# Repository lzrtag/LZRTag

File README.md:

# LZRTag
### ESP32-Based Lasertag

Ever wanted to set up your own system of Lasertag?
Interested in having an easily modifiable system to create your own gamemodes and styles with?
Or just looking for a cool project to try out?
Well, why not take a spin at this!

*Note:* This project is not in serious development. I (Xasin) take no responsibility for what is done with this code, and I can't guarantee it'll do exactly what I tell it to (even if I try to give it treats >:c)
However, it is a fully functional system, if you know how to use it, and it has proven itself
to be pretty reliable and useful!

## The components
In order to have a functional game, you will need at least the following:
- Two or more soldered Lasertag Sets
- A WiFi access point or a newtwork of points throughout the arena.
- A MQTT Server, preferrably in the local network, to reduce ping.
- And a system running Ruby 2.4 or better, to run the Lasertag Backend and your gamemodes

## The Electronics
*Attention:* The electronics aren't necessarily beginner-friendly. I've designed them with components no smaller than a TSOP package or a 0805 resistor, but the newer versions of the hardware do include two QFN Packages - one for a optional IMU, so it can be left out, and one for a standard I2S audio chip, for which you can use any breakout board that supports 44100Hz, 16 bit playback. If you have a hot air gun,
definitely make use of it!

The electronics are based around the ESP32, a fairly cheap, powerful, WiFi and Bluetooth capable chip. The PCB includes all necessary support structures, including a battery charge circuit and a USB to UART converter to reprogram and debug the ESP.
It comes with the following hardware:
- The ESP32 plus beefy voltage regulation, ESD protection, etc. It ain't gonna break!
- A MAX I2S decoder + amplifier, for on-board, high quality audio.
- A LSM6D IMU, to detect movement, collisions, gestures, etc.
- Peripherals to receive and send IR Signals (documented here: TODO)
- Feedback in the shape of WS2812 LEDs and a vibration motor
- Trigger, Gun Select and Reload buttons.

The vest connection is exposed with a D-SUB connector, and I2C lines are available to make
more complex add-ons easier to achieve. There's also a I2C breakout connection on the PCB itself!

The Vest itself can be as simple as a couple of Vishay 40kHz IR receivers and WS2812 LEDs, but
there is a connection for vest-specific haptic feedback, and via the I2C connection it's easy to add
more complex features.

To solder one, check out the Aisler project here: https://aisler.net/p/QLILZEMV
Or head to the "Electronics" folder and generate your own Gerber files!

## The Casing
The 3D printed casing I designed is totally optional - the electronics can be easily fitted into any other casing, provided it has space for a switch, a speaker and a couple of LEDs!
However, if you do want to print it out, there's the Fusion360 page here: https://a360.co/2Lbm2zJ

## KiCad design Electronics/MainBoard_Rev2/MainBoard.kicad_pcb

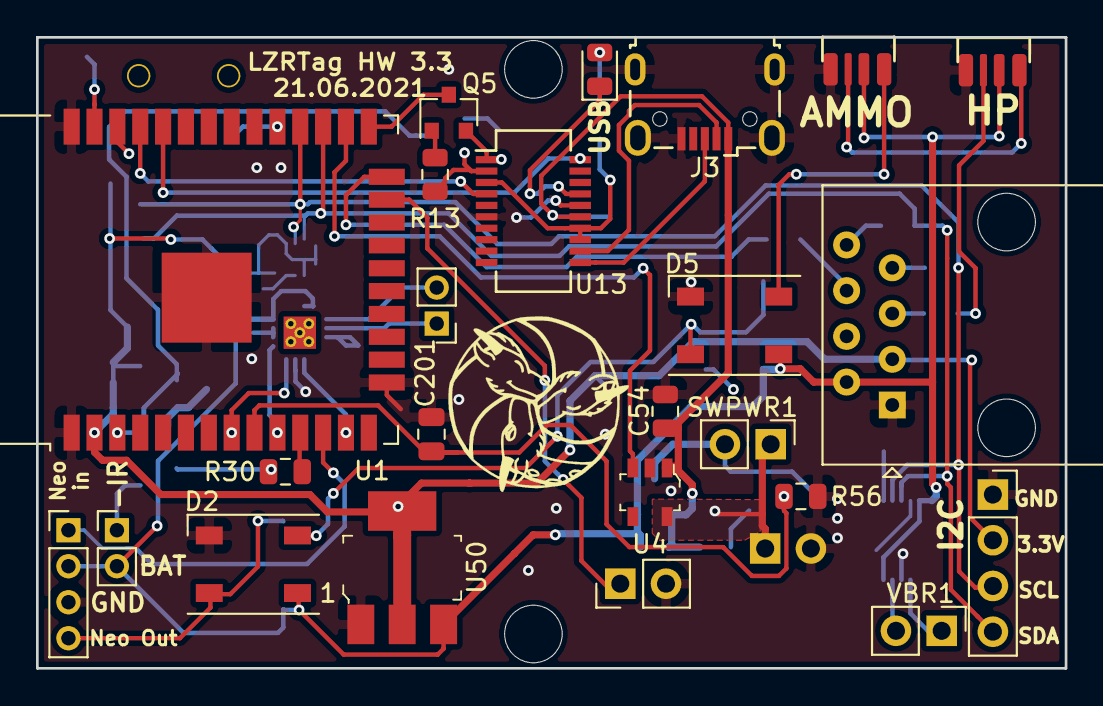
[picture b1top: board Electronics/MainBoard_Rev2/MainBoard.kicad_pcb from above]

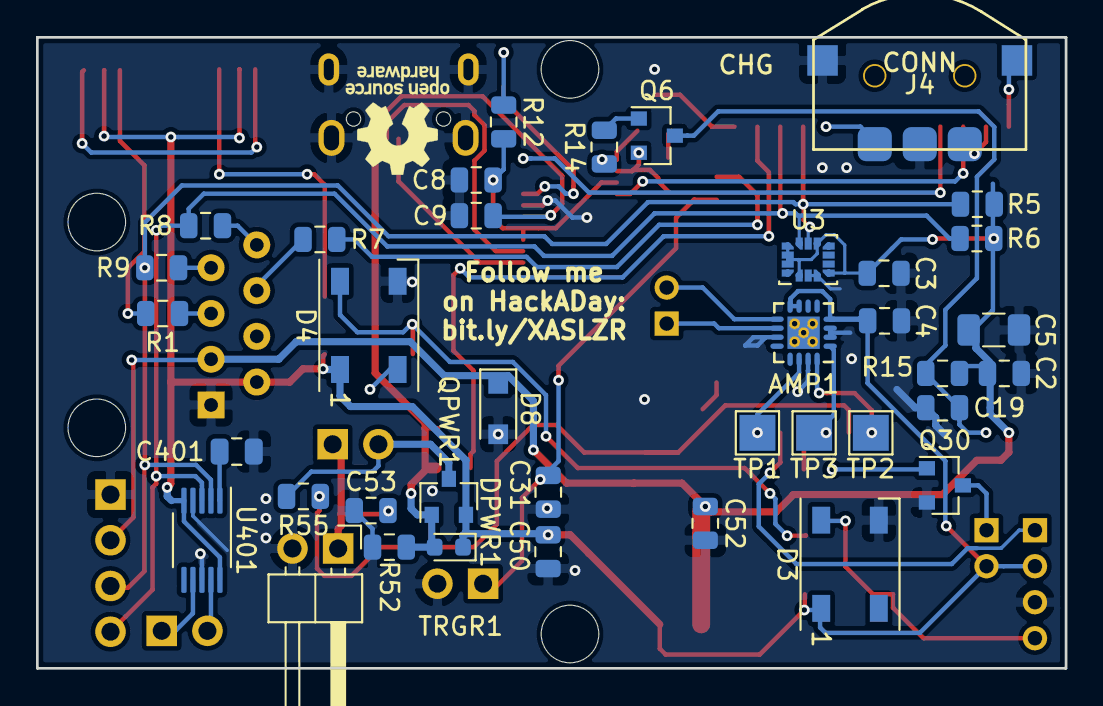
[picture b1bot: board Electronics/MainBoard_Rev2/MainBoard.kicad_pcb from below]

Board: 2 copper layers, 57.2 x 35.1 mm, 67 parts (40 on the bottom side), 49 nets.

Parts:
AMP1: MAX98357A; QFN-16-1EP_3x3mm_P0.5mm_EP2.7x2.7mm_ThermalVias
BT1: Battery_Cell; PinHeader_1x02_P2.54mm_Horizontal
C2, C3, C8, C19, C31: 100nF; C_0805_2012Metric
C4, C9, C52, C53: 10uF; C_0805_2012Metric
C5: 47uF; C_1206_3216Metric
C50, C54, C401: 1uF; C_0805_2012Metric
C201: 0.1uF; C_0805_2012Metric
D1: COM-12999; PinHeader_1x04_P2.00mm_Vertical
D2, D3, D4, D5: WS2812B; LED_WS2812B_PLCC4_5.0x5.0mm_P3.2mm
D8: D_Zener_ALT; D_SOD-123F
D30: SFH4545; PinHeader_1x02_P2.00mm_Vertical
D401, D402: IN-PI42TAS
DPWR1: D_Schottky; D_0603_1608Metric
DUSB1: LED; LED_0805_2012Metric
H1, H2: MountingHole; MountingHole_3.2mm_M3_DIN965
H3: MountingHole; KiCad-Logo_5mm_SolderMask
H4: MountingHole; OSHW-Logo_5.7x6mm_SilkScreen
H6: MountingHole; DragonIcon
J1: Conn_01x04_Female; PinSocket_1x04_P2.54mm_Vertical
J3: USB_B_Micro; USB_Micro-B_Wuerth_629105150521
J4: Conn_01x04_Male; nav_switch_COM_08184
J5: Conn_01x02_Male; PinHeader_1x02_P2.00mm_Vertical
J101: 54602-908LF; RJ45_Amphenol_54602-x08_Horizontal
Q5, Q6: Q_NPN_BEC; SOT-23
Q30: PMBT2222A; SOT-23
QPWR1: IRLML6402; SOT-23
R1, R7, R8, R9, R30: 220R; R_0805_2012Metric
R5, R6: 2.2k; R_0805_2012Metric
R12: 220; R_0805_2012Metric
R13, R14, R52: 10k; R_0805_2012Metric
R15: R_Small; R_0805_2012Metric
R55, R56: 50k; R_0805_2012Metric
SWPWR1: SW_SPST; PinHeader_1x02_P2.54mm_Vertical
TP1, TP2, TP3: TestPoint; TestPoint_Pad_2.0x2.0mm
TRGR1: SW_Push; PinHeader_1x02_P2.54mm_Vertical
U1: ESP32-WROOM-32
U3: LSM6DSMTR; LGA-14_3x2.5mm_P0.5mm_LayoutBorder3x4y
U4: MAX1555EZK_T; SOT-753
U13: FT231XS; SSOP-20_3.9x8.7mm_P0.635mm
U50: AP2114H-3_3TRG1; SOT-223
U401: DRV2605; VSSOP-10_3x3mm_P0.5mm
VBR1: Motor_DC_ALT; PinHeader_1x02_P2.54mm_Vertical

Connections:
+3V3: C2.1, C3.2, C5.2, C52.1, D8.1, J1.2, J101.3, R5.1, R6.1, R15.1, U1.2, U3.1, U3.2, U3.3, U3.5, U3.8, U3.12, U50.2, U50.4
+BATT: AMP1.4, AMP1.7, AMP1.8, C4.1, C50.1, D1.2, D2.1, D3.1, D4.1, D5.1, D30.2, D401.1, D402.1, DPWR1.1, J101.2, QPWR1.2, U50.3, U401.5, U401.10
/AUDIO: AMP1.1, TP3.1, U1.10
/BCLK: AMP1.16, TP2.1, U1.8
/CHG_STAT: U1.26, U4.3
/CTRL_BACK: J4.1, U1.29
/CTRL_DOWN: J4.4, U1.37
/CTRL_FWD: J4.3, U1.36
/E>U: U1.35, U13.4
/GPIO0: Q5.3, U1.25
/IR_IN: R7.2, U1.24
/IR_OUT: R30.2, U1.11
/LED_1: D1.1, U1.12
/LED_2: D402.2, R1.2
/LRCLK: AMP1.14, TP1.1, U1.13
/PowerHandling/B_Raw+: QPWR1.3, R55.1, SWPWR1.2
/RESET: C19.1, Q6.3, R15.2, U1.3
/TRIGGER: C31.1, TRGR1.1, U1.23
/U>E: U1.34, U13.20
/USB Connection/+5V_USB: C9.2, C54.1, DPWR1.2, J3.1, QPWR1.1, R52.1, U4.1, U13.15
/USB Connection/USB3.3: C8.2, R12.1, U13.3, U13.13, U13.14
/V_SENSE: C201.1, R55.2, R56.1, U1.9
GND: AMP1.2, AMP1.3, AMP1.11, AMP1.15, BT1.2, C2.2, C3.1, C4.2, C5.1, C8.1, C9.1, C19.2, C31.2, C50.2, C52.2, C53.2, C54.2, C201.2, C401.2, D1.3, D2.3, D3.3, D4.3, D5.3, D8.2, D401.3, D402.3, J1.1, J3.5, J3.6, J4.2, J101.1, Q30.2, R52.2, R56.2, TRGR1.2, U1.1, U1.15, U1.38, U1.39, U3.6, U3.7, U4.2, U13.6, U13.16, U50.1, U401.4, U401.8
unnamed: AMP1.9, J5.2
unnamed: AMP1.10, J5.1
unnamed: BT1.1, C53.1, SWPWR1.1, U4.5
unnamed: C401.1, U401.1
unnamed: D1.4, D2.4, D3.4
unnamed: D2.2, D4.4, D5.4
unnamed: D30.1, Q30.3
unnamed: D401.2, D402.4
unnamed: D5.2, D401.4
unnamed: DUSB1.1, U13.17
unnamed: DUSB1.2, R12.2
unnamed: J3.2, U13.12
unnamed: J3.3, U13.11
unnamed: J101.5, R1.1
unnamed: J101.6, R7.1
unnamed: J101.7, R9.1
unnamed: J101.8, R8.1
unnamed: Q5.1, R13.1
unnamed: Q5.2, R14.2, U13.1
unnamed: Q6.1, R14.1
unnamed: Q6.2, R13.2, U13.2
unnamed: Q30.1, R30.1
unnamed: U401.7, VBR1.1
unnamed: U401.9, VBR1.2
SCL: J1.3, R5.2, R9.2, U1.28, U3.13, U401.2
SDA: J1.4, R6.2, R8.2, U1.27, U3.14, U401.3

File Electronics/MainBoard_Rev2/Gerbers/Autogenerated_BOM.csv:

"Id";"Designator";"Package";"Quantity";"Designation";"Supplier and ref";
1;"BT1";"PinHeader_1x02_P2.54mm_Horizontal";1;"Battery_Cell";;;
2;"D402,D401";"IN-PI42TAS";2;"IN-PI42TAS";;;
3;"J101";"RJ45_Amphenol_54602-x08_Horizontal";1;"54602-908LF";;;
4;"D30";"PinHeader_1x02_P2.00mm_Vertical";1;"SFH4545";;;
5;"D1";"PinHeader_1x04_P2.00mm_Vertical";1;"COM-12999";;;
6;"C401,C50,C54";"C_0805_2012Metric";3;"1uF";;;
7;"C201";"C_0805_2012Metric";1;"0.1uF";;;
8;"U401";"VSSOP-10_3x3mm_P0.5mm";1;"DRV2605";;;
9;"R8,R9,R1,R7,R30";"R_0805_2012Metric";5;"220R";;;
10;"J5";"PinHeader_1x02_P2.00mm_Vertical";1;"Conn_01x02_Male";;;
11;"TP1,TP2,TP3";"TestPoint_Pad_2.0x2.0mm";3;"TestPoint";;;
12;"C5";"C_1206_3216Metric";1;"47uF";;;
13;"D8";"D_SOD-123F";1;"D_Zener_ALT";;;
14;"J4";"nav_switch_COM_08184";1;"Conn_01x04_Male";;;
15;"C4,C52,C9,C53";"C_0805_2012Metric";4;"10uF";;;
16;"AMP1";"QFN-16-1EP_3x3mm_P0.5mm_EP2.7x2.7mm_ThermalVias";1;"MAX98357A";;;
17;"C2,C31,C8,C19,C3";"C_0805_2012Metric";5;"100nF";;;
18;"R6,R5";"R_0805_2012Metric";2;"2.2k";;;
19;"R52,R13,R14";"R_0805_2012Metric";3;"10k";;;
20;"R55,R56";"R_0805_2012Metric";2;"50k";;;
21;"U4";"SOT-753";1;"MAX1555EZK_T";;;
22;"J3";"USB_Micro-B_Wuerth_629105150521";1;"USB_B_Micro";;;
23;"DUSB1";"LED_0805_2012Metric";1;"LED";;;
24;"U13";"SSOP-20_3.9x8.7mm_P0.635mm";1;"FT231XS";;;
25;"Q5,Q6";"SOT-23";2;"Q_NPN_BEC";;;
26;"R12";"R_0805_2012Metric";1;"220";;;
27;"R15";"R_0805_2012Metric";1;"R_Small";;;
28;"U50";"SOT-223";1;"AP2114H-3_3TRG1";;;
29;"U3";"LGA-14_3x2.5mm_P0.5mm_LayoutBorder3x4y";1;"LSM6DSMTR";;;
30;"H6";"DragonIcon";1;"MountingHole";;;
31;"H3";"KiCad-Logo_5mm_SolderMask";1;"MountingHole";;;
32;"H4";"OSHW-Logo_5.7x6mm_SilkScreen";1;"MountingHole";;;
33;"J1";"PinSocket_1x04_P2.54mm_Vertical";1;"Conn_01x04_Female";;;
34;"H2,H1";"MountingHole_3.2mm_M3_DIN965";2;"MountingHole";;;
35;"SWPWR1";"PinHeader_1x02_P2.54mm_Vertical";1;"SW_SPST";;;
36;"DPWR1";"D_0603_1608Metric";1;"D_Schottky";;;
37;"TRGR1";"PinHeader_1x02_P2.54mm_Vertical";1;"SW_Push";;;
38;"VBR1";"PinHeader_1x02_P2.54mm_Vertical";1;"Motor_DC_ALT";;;
39;"D4,D5,D3,D2";"LED_WS2812B_PLCC4_5.0x5.0mm_P3.2mm";4;"WS2812B";;;
40;"Q30";"SOT-23";1;"PMBT2222A";;;
41;"QPWR1";"SOT-23";1;"IRLML6402";;;
42;"U1";"ESP32-WROOM-32";1;"ESP32-WROOM-32";;;

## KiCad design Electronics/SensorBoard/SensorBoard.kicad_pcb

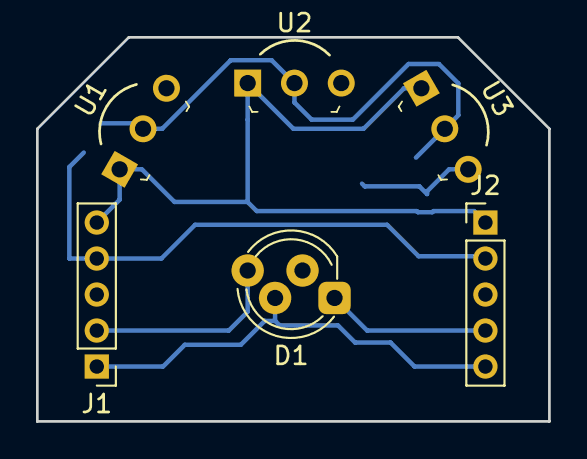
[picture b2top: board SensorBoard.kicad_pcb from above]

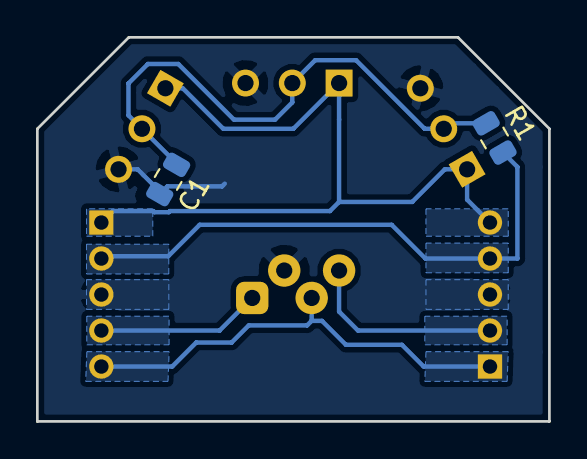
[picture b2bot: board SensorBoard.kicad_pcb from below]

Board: 2 copper layers, 28.4 x 21.3 mm, 8 parts (2 on the bottom side), 7 nets.

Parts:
C1: C_Small; C_0805_2012Metric
D1: NeoPixel_THT; LED_D5.0mm-4_RGB_Staggered_Pins
J1, J2: Conn_01x05_Male; PinHeader_1x05_P2.00mm_Vertical
R1: R_Small; R_0805_2012Metric
U1, U2, U3: TSSP58038; TO-92-3_Formed_Leads

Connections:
+3V3: J1.4, J2.2, R1.2
+BATT: D1.3, J1.1, J2.5
GND: C1.2, D1.2, J1.3, J2.3, U1.3, U2.3, U3.3
unnamed: C1.1, R1.1, U1.2, U2.2, U3.2
unnamed: D1.1, J2.4
unnamed: D1.4, J1.2
unnamed: J1.5, J2.1, U1.1, U2.1, U3.1

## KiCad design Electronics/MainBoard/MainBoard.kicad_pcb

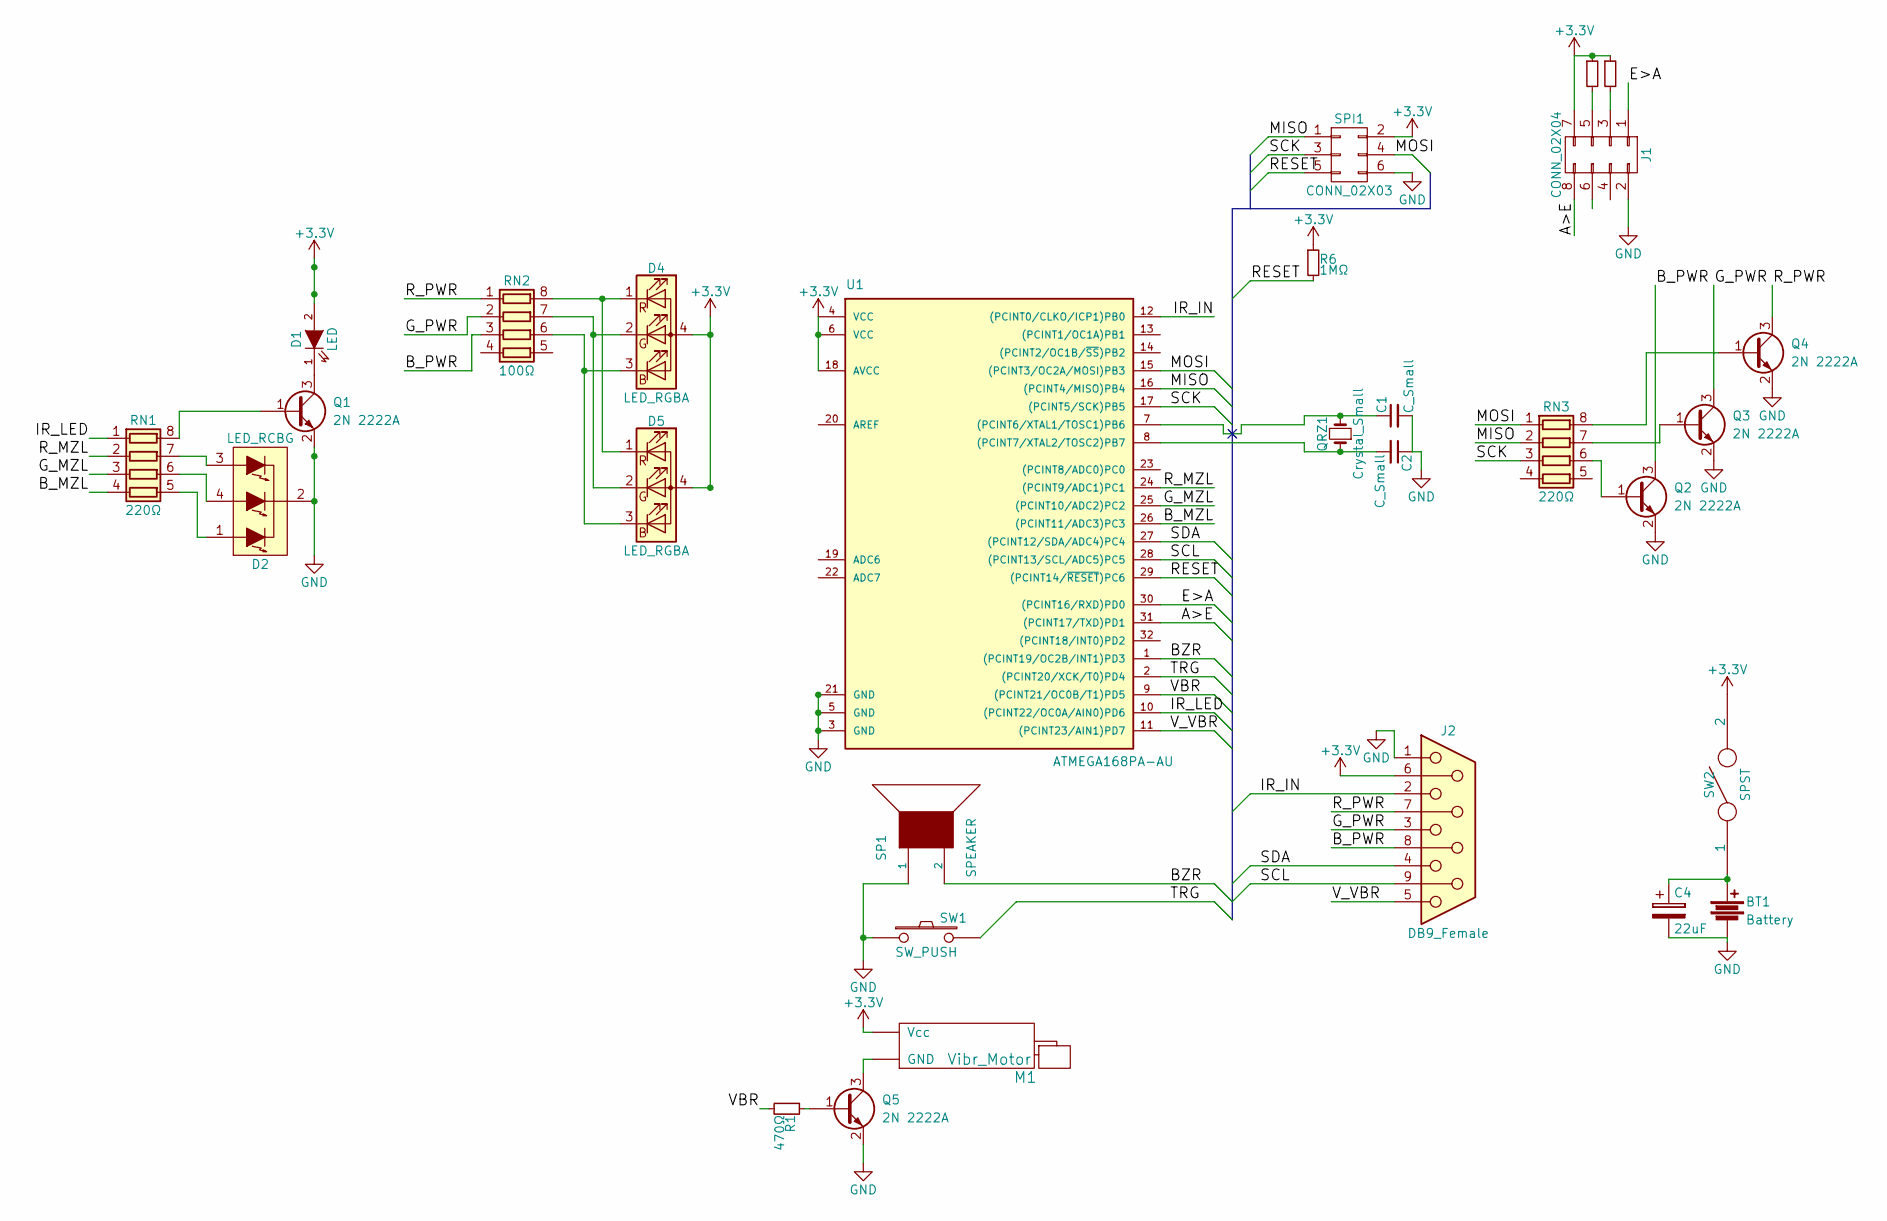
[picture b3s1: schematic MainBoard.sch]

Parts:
BT1: Battery; JST_PH_S2B-PH-K_02x2.00mm_Angled
C1, C2: C_Small; C_0603_HandSoldering
C4: 22uF; CP_Elec_5x5.3
D1: LED; LED_D3.0mm_Horizontal_O1.27mm_Z10.0mm
D2: LED_RCBG; LED_D5.0mm-4
D4, D5: LED_RGBA; LED_Cree-PLCC4_3.2x2.8mm_CCW
J1: CONN_02X04; Pin_Header_Straight_2x04_Pitch2.54mm
J2: DB9_Female; DSUB-9_Female_Horizontal_Pitch2.77x2.84mm_EdgePinOffset4.94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
M1: Vibr_Motor; SolderWirePad_2x_0-8mmDrill
Q1, Q2, Q3, Q4, Q5: 2N 2222A; SOT-23_Handsoldering
QRZ1: Crystal_Small; Crystal_HC49-U_Vertical
R1: 470Ω; R_0603_HandSoldering
R6: 1MΩ; R_0603_HandSoldering
R9, R11: RST; R_0603_HandSoldering
RN1, RN3: 220Ω; R_Array_Convex_4x1206
RN2: 100Ω; R_Array_Convex_4x1206
SP1: SPEAKER; Buzzer_15x7.5RM7.6
SPI1: CONN_02X03; Pin_Header_Straight_2x03_Pitch2.54mm
SW1: SW_PUSH; SolderWirePad_2x_0-8mmDrill
SW2: SPST; Pin_Header_Straight_1x03_Pitch2.54mm
U1: ATMEGA168PA-AU; TQFP-32_7x7mm_Pitch0.8mm

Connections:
+3V3: D1.2 (A), D4.4 (A), D5.4 (A), J1.7, J2.6, M1.2 (Vcc), R6.1, R9.1, R11.1, SPI1.2, SW2.2, U1.4 (VCC), U1.6 (VCC), U1.18 (AVCC)
/A>E: J1.8, U1.31 ((PCINT17/TXD)PD1)
/BZR: SP1.2, U1.1 ((PCINT19/OC2B/INT1)PD3)
/B_MZL: RN1.4 (R4.1), U1.26 ((PCINT11/ADC3)PC3)
/B_PWR: J2.8, Q2.3 (C), RN2.3 (R3.1)
/E>A: J1.1, U1.30 ((PCINT16/RXD)PD0)
/G_MZL: RN1.3 (R3.1), U1.25 ((PCINT10/ADC2)PC2)
/G_PWR: J2.3, Q3.3 (C), RN2.2 (R2.1)
/IR_IN: J2.2, U1.12 ((PCINT0/CLKO/ICP1)PB0)
/IR_LED: RN1.1 (R1.1), U1.10 ((PCINT22/OC0A/AIN0)PD6)
/MISO: RN3.2 (R2.1), SPI1.1, U1.16 ((PCINT4/MISO)PB4)
/MOSI: RN3.1 (R1.1), SPI1.4, U1.15 ((PCINT3/OC2A/MOSI)PB3)
/RESET: R6.2, SPI1.5, U1.29 ((PCINT14/~RESET~)PC6)
/R_MZL: RN1.2 (R2.1), U1.24 ((PCINT9/ADC1)PC1)
/R_PWR: J2.7, Q4.3 (C), RN2.1 (R1.1)
/SCK: RN3.3 (R3.1), SPI1.3, U1.17 ((PCINT5/SCK)PB5)
/SCL: J2.9, U1.28 ((PCINT13/SCL/ADC5)PC5)
/SDA: J2.4, U1.27 ((PCINT12/SDA/ADC4)PC4)
/TRG: SW1.2, U1.2 ((PCINT20/XCK/T0)PD4)
/VBR: R1.2, U1.9 ((PCINT21/OC0B/T1)PD5)
/V_VBR: J2.5, U1.11 ((PCINT23/AIN1)PD7)
GND: BT1.2, C1.2, C2.1, C4.2, D2.2 (COMMON_CATHODE), J1.2, J2.1, Q1.2 (E), Q2.2 (E), Q3.2 (E), Q4.2 (E), Q5.2 (E), SP1.1, SPI1.6, SW1.1, U1.3 (GND), U1.5 (GND), U1.21 (GND)
unnamed: BT1.1, C4.1, SW2.1
unnamed: C1.1, QRZ1.2, U1.7 ((PCINT6/XTAL1/TOSC1)PB6)
unnamed: C2.2, QRZ1.1, U1.8 ((PCINT7/XTAL2/TOSC2)PB7)
unnamed: D1.1 (K), Q1.3 (C)
unnamed: D2.1 (RED_ANODE), RN1.5 (R4.2)
unnamed: D2.3 (BLUE_ANODE), RN1.7 (R2.2)
unnamed: D2.4 (GREEN_ANODE), RN1.6 (R3.2)
unnamed: D4.1 (RK), D5.1 (RK), RN2.8 (R1.2)
unnamed: D4.2 (GK), D5.2 (GK), RN2.7 (R2.2)
unnamed: D4.3 (BK), D5.3 (BK), RN2.6 (R3.2)
unnamed: J1.3, R11.2
unnamed: J1.5, R9.2
unnamed: M1.1 (GND), Q5.3 (C)
unnamed: Q1.1 (B), RN1.8 (R1.2)
unnamed: Q2.1 (B), RN3.6 (R3.2)
unnamed: Q3.1 (B), RN3.7 (R2.2)
unnamed: Q4.1 (B), RN3.8 (R1.2)
unnamed: Q5.1 (B), R1.1

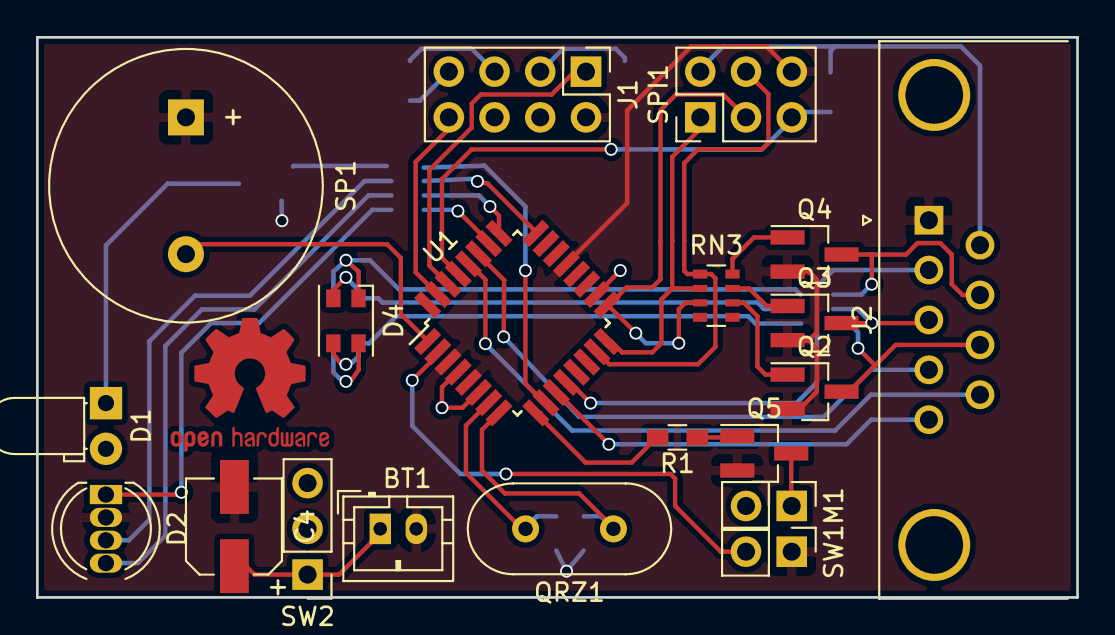
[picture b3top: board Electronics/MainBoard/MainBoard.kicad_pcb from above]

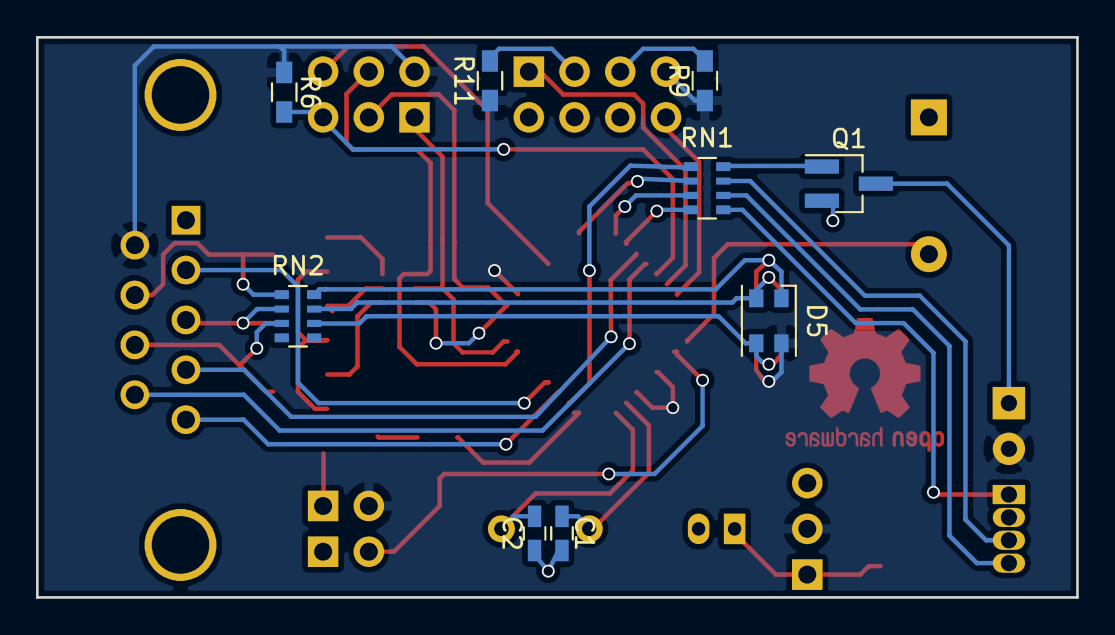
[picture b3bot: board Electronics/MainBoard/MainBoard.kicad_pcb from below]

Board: 2 copper layers, 57.8 x 31.1 mm, 29 parts (9 on the bottom side), 40 nets.

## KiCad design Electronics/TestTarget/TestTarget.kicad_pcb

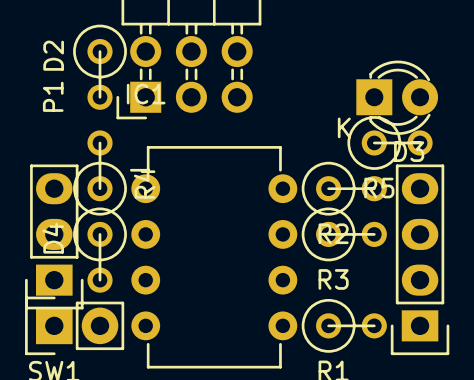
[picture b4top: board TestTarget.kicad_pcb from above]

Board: 2 copper layers, 13 parts (0 on the bottom side), 13 nets, no tracks yet.

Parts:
BT1: Battery; Pin_Header_Straight_1x02
D1: LED_RCBG; Pin_Header_Straight_1x04
D2, D4: D; R1
D3: LED-G; LED-3MM
IC1: ATTINY13A-P; DIP-8_W7.62mm
P1: CONN_02X03; Pin_Header_Angled_2x03
R1, R2, R3: 470Ω; R1
R4: 1MΩ; R1
R5: 5KΩ; R1
SW1: SPST; Pin_Header_Straight_1x03

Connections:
+3V3: D2.2, D4.1, IC1.8, R4.2, R5.1
/MISO/G: IC1.6, P1.1, R2.1
/MOSI/R: IC1.5, P1.4, R3.1
/SCK/B: IC1.7, P1.3, R1.1
GND: BT1.2, D1.2, D3.1, IC1.4, P1.6
unnamed: BT1.1, SW1.1
unnamed: D1.1, R1.2
unnamed: D1.3, R3.2
unnamed: D1.4, R2.2
unnamed: D2.1, P1.2
unnamed: D3.2, R5.2
unnamed: D4.2, SW1.2
unnamed: IC1.1, R4.1

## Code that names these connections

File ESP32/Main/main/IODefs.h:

/*
 * IODefs.h
 *
 *  Created on: 7 Jan 2019
 *      Author: xasin
 */

#ifndef MAIN_IODEFS_H_
#define MAIN_IODEFS_H_

#define PIN_I2C_SDA GPIO_NUM_16
#define PIN_I2C_SCL GPIO_NUM_17

#define PIN_IR_OUT	GPIO_NUM_33
#define PIN_IR_IN	GPIO_NUM_35

#define PIN_I2S_DATA GPIO_NUM_25
#define PIN_I2S_BLCK GPIO_NUM_32
#define PIN_I2S_LRCK GPIO_NUM_14

#define PIN_VBRT	GPIO_NUM_13

#define PIN_TRIGR	GPIO_NUM_22

#define PIN_BAT_MES 	GPIO_NUM_2
#define ADC_BAT_MES		ADC1_CHANNEL_5
#define PIN_BAT_CHGING	GPIO_NUM_4

#define PIN_WS2812_OUT	GPIO_NUM_27
#define WS2812_NUMBER 	4

#define PIN_BAT_GREEN	GPIO_NUM_34
#define PIN_BAT_RED		GPIO_NUM_18

#define PIN_CONN_IND	GPIO_NUM_21

#define PIN_CTRL_FWD	GPIO_NUM_2
#define PIN_CTRL_BACK	GPIO_NUM_0
#define PIN_CTRL_DOWN	GPIO_NUM_4
#endif /* MAIN_IODEFS_H_ */

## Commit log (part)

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2018-11-14 Added a map set
2018-11-15 Finished merge
2018-11-15 Began integrating map and made rudimentary map-parsing
2018-11-15 Added zone data
2018-11-15 Added zone data and debug messages
2018-11-18 Small fixes to the zone system
2018-11-18 Parsed map coordinates to floats
2018-11-18 Added centerpoint data
2018-11-18 Tested map pushing
2018-11-18 Fixed polygon assigment bug
2018-11-18 Added poly debug output
2018-11-19 Tweaking out a few more bugs
2018-11-22 Exposed polygon points and zones via count system
2019-01-01 not even sure, probably map adjustments <3
2019-01-01 Rubocop fixes, thanks Codacy
2019-01-01 Last fixes for the main merge
2019-01-02 Began working on hardware R3
2019-01-05 Rev 3.0 is now done!
2019-01-07 Added STEP model
2019-01-07 Set up a basic HelloWorld
2019-01-07 Slowly setting up environment
2019-01-09 Tried to get Light Sleep LEDC to work
2019-01-09 Added new KConf for modules
2019-01-11 Began playing with BT BLE code
2019-01-11 Adjusted main code for BLE
2019-01-11 Testing light sleep derp stuff
2019-01-19 Began working on ze gun!
2019-01-21 Added mane animation, test sound playing
2019-01-23 Began adjusting code
2019-01-24 Adjusted a few resistor values, added I2S pinout
2019-01-25 Lotsa playing around
2019-01-27 Added a weapon, the wyre. Whee!
2019-01-30 Started working on the housekeeping ticks
2019-01-30 Began working on charge output
2019-02-01 Began adding better visual feedback
2019-02-18 Began working on the IR code
2019-02-25 Changed start frame to be more recognizable
2019-02-25 Modified IR code to work
2019-02-25 Included IR code in setup routine
2019-02-25 Began debugging + playing with IR code
2019-02-28 Smol cleanup
2019-02-28 Added some logging information
2019-02-28 Added MQTT connection
2019-02-28 Played with a few start beeps
2019-02-28 Wifi power reduction
2019-02-28 Began working on new classes for nice flashy stuff <3
2019-03-01 Small tweaks and tests :>
2019-03-15 Tweaked Wyre, added standard team colors
2019-03-16 Added hit flash
2019-03-19 Added player class and team setting
2019-03-25 Added brightness levels and player integration of them
2019-04-11 Added proper MQTT connections <3
2019-04-11 Raw sound files included!
2019-04-22 Removed old ESPComs files
2019-04-22 Adjusted AVR code for the new checksum
2019-04-24 Added proper MQTT connections
2019-04-25 Adjustments to the AVR-Side RX code
2019-04-25 Changed MQTT Topics to FX/+
2019-04-25 Added some sound stuff :D
2019-04-26 Small reworks to keep compatibility
2019-04-26 Finalisations to the R3 tweaks
2019-04-26 Small random-team assingment tweak
2019-04-28 Added sensing of whether or not the player is marked
2019-04-28 Small visual fixes
2019-04-28 Clean-up and more visual comments
2019-04-28 Visual feedback part of the marking
2019-04-28 Random smol changes
2019-04-28 Removed unnecessary Bluetooth include
2019-04-28 Added paused ammo sending for less MQTT load
2019-04-28 Switched to compiled lua, added 'marked' feature
2019-04-28 Smal fixes
2019-04-28 Added hook rescues
2019-04-28 Reverted to Lasertag Raspberry and tuned some speeds :>
2019-04-28 Added ruby integration for FX-Marking
2019-05-08 Small tweaks and fixes here and there
2019-05-08 Added TWO new weapons and lotsa pew pew sounds
2019-05-10 Removed include
2019-05-10 Adjustments for per-weapon ammo
2019-05-10 Removal of defaultGun, use of per-weapon ammo, proper reload sound
2019-05-10 Small fixes for #47
2019-05-12 Switched to "1"/"0" instead of "true"/"false" for consistency
2019-05-12 Smol extra feature for the Damager hook
2019-05-12 Added a gunDamageMultiplier with reasonable DPS adjustment Already integrated into the standard damager hook!
2019-05-12 Added proper Readme
2019-05-12 Version bump for the gem, ready to push!
2019-07-08 Update README.md
    Began working on a nicer README, for that cute HackADay project someone is working on ^^
2019-07-11 Began rework to even better hardware
2019-07-11 Fixed footprint assignment
2019-07-11 MORE
2019-07-17 Began preparing a branch for HackADay users
2019-07-26 Added a nicer file to change LZRTag options
2019-08-27 Small tweaks to the PlayerBase topic (now uses 0 instead of space)
2019-08-29 Began reworking the PCB
2019-08-29 Small tweak to gitignore to allow symbol caches
2019-08-29 Added nav switch models
2019-08-29 Began reworking sections
2019-08-30 Continued work on the current electronics
2019-09-05 Began working on much better lights
2019-09-05 Small adjustments
2019-09-06 Finished the first batch of time and position-functions
2019-09-08 Added enable/disable and convenience functions
2019-09-08 Played with test code a bit
2019-09-09 Began adding standard patterns
2019-09-12 Tweaked to provide new brightness parameters
2019-09-12 Split up pattern changing into files, added patterns
2019-09-12 Began working on safer shutdown procedures
2019-09-12 Added charging patter
2019-09-12 Reduced WiFi power to prevent brownouts
2019-09-12 Added variable color marking and player 'get_marked_color'
2019-09-19 fix important issues found during review
2019-09-19 adjust ShotFlicker to allow arbitrary length and point count
2019-09-19 add mandatory main loop delay
2019-09-19 Add a little documentation to VestPattern arguments
2019-09-19 Resolve remaining review errors
2019-09-19 tweak "CHARGING" pattern brightness
2019-09-19 add pin init
2019-09-19 Add nav switch read function
    Special care has to be taken for read order, due to
    false but workable wiring.
    Capacitive charging due to low pullups require the PIN_CTRL_DOWN pin to
    be pulled high as much as possible
2019-09-19 Speed up housekeeping_thread for faster HW reads
2019-09-19 Add NavSwitch reading to Housekeeping
2019-09-20 fix the MQTT pub path
2019-09-20 Add team selector to the test game
2019-09-20 Add MAC-based player ID, #57
2019-09-20 Fix wrong use of player.deviceID
    Due to it now not being const, a getter function will instead be used
2019-09-22 adjust brightness key handling.
    The new system uses one central definition for the brightness keys, and
    changes @brightness to be a symbol too
2019-09-22 Change the standard hook to use the new brightness
2019-09-22 Add a counter handler for brightness levels
2019-09-22 Adjust the MQTT server connection
2019-09-22 Adjust the animation values a bit
2019-09-22 Fix bug in how players are counted
2019-09-22 Tweak the test script
2019-09-24 Lots of changes for playing a MiDi file! Good stuff
2019-09-25 Initialize the IMU and I2C properly
2019-09-25 Move gyro handling to a separate file
2019-09-25 Add Lasertag position detection
2019-09-25 Change gyro MQTT Topic
2019-09-25 Add gyro retain flag
2019-09-25 Fix marking disabling
2019-09-25 Add a bit of testing for the Gyro
2019-09-25 Remove unnecessary cmath include
2019-09-27 Change MQTT topics to the improved layout
2019-09-27 Add new vibration command
2019-09-27 Improve sound and noise handling
    Yay for an extra interface!
2019-09-27 Change base game's noise
2019-09-29 Improve vibration handling
    This new way completely prioritizes certain vibration types. Before,
    various modes of vibration could've still mixed together awkwardly.
2019-10-01 Add handling of game phases
2019-10-01 Allow the game class to receive events
    Instead of hooking in the game as another hook, it gets a custom
    handling for better performance
2019-10-01 Remove redacted, non-phase functions
2019-10-01 Implement new SDL functions to let users define phases more easily
2019-10-02 Add a phase ending hook
2019-10-02 Add a much better way of integrating hooks
2019-10-02 Improve Hook initialization
    The new system has to pass a reference to the handler down to the hook,
    and uses a more general **option hash
2019-10-02 Add a proper, error-reporting rescue
2019-10-02 Add a clean way of setting the next phase
2019-10-02 Add a centralized list of in-game players This way, we don't have to rely on their teams, connection status, etc.
2019-10-02 Tesssst the new stuff :D
2019-10-02 Integrate game-specific hooks into Hit Arbitration
2019-10-10 Give Housekeeping a bit more RAM
2019-10-10 Handle fetching the phase better
2019-10-10 Adjust phase speed and phase list
2019-10-10 Add a method to let users register games with names
2019-10-10 Improve game phase switching
    By providing better allowed phase fetching as well as a proper @lastTick
    timer reset
2019-10-10 Register and auto-stop the game
2019-10-10 Move countdown phase a little
2019-10-12 Tweak the game to improve performance
    For some reason, the Puts at the Lasertag init is necessary in order to
    start MQTT
    How this works ... I have no clue.
2019-10-12 Tweak the test game to not start with players still selecting
2019-10-15 Switched back to local Raspi server
2019-10-16 Begin work on the single-sided sensor board
2019-10-16 Fix small nitpicks from PR #68
2019-10-17 Begin work on code documentation
2019-10-17 Document the base game functionality
2019-10-18 Document the core handler classes
2019-10-18 Add yardopts and gitignore
2019-10-18 Add a event symbol description
2019-10-18 Finish documenting the player classes
2019-10-18 Document the base hook class
2019-10-18 Reorder phase changing a tiny bit
2019-10-18 Add most of the regular event symbols
2019-10-18 Add an event on gun change
2019-10-19 Complete the event symbol documentation
2019-10-19 Adjust the life player to include reviving by player
2019-10-19 Add README
2019-10-19 Add whitespace around code examples
2019-10-20 Fix a few typos
2019-10-20 Move HookList from Array to Hash
2019-10-20 Update the test script
2019-10-20 Perform one last tweak
2019-10-23 Replace DIY IR handling with XIRR library
2019-10-23 Modify ruby to use the new hit topic
2019-10-23 Add a "slowTick" to process beacon timings
2019-10-23 Add a 'lil documentation
2019-10-23 Add a counter for player beacon distribution
2019-10-23 Add auto-generated stuff
2019-10-23 Add beacon use for team selection
2019-10-23 Change MQTT server used to test
2019-10-23 Continue documenting MQTT Topics
2019-10-23 Fix urgent typo
2019-10-23 Tweak test script a little
2019-10-23 Fix debug hook not passing handler
2019-10-23 Fix typo
2019-10-29 Improve connection/disconnect detection
2019-10-29 Add LZROptions file for easier config
2019-10-29 Begin work on a new reloading and switching mechanism
2019-10-30 Adjust weapon profiles
2019-10-30 Add commenting
2019-10-30 Add a opt-out from charge mode
2019-10-30 Add a ' ' push to message clearing
2019-11-01 Replace emptyClickPlayed with ShotAlreadyHandled for more functionalit
2019-11-01 Tweak wyre a little more
2019-11-01 Add a reload flag to let Server-side reload
2019-11-01 Fix a typo in hit arb handling
2019-11-03 Begin work on a gun selector class
2019-11-03 Add ammo setter functions
2019-11-03 Change player QOS
2019-11-03 Add a Deny sound
2019-11-03 Remove global sound mute
2019-11-03 Fix MQTT Topic comparison
2019-11-03 Improve sound playback
2019-11-04 Add and use a gun selector Hook
2019-11-04 Add convenience wrappers for state changes
2019-11-04 Remove a infinite reload-related loop
2019-11-04 Tweak code a little for PR #76
2019-11-08 Begin work on a statistics player
2019-11-09 Add fancy terminal-based outputs :>
2020-08-22 Change a few names to use DigiKey Part Number
2020-12-26 Begin work on using new IDF 4.1 Style env
2021-01-30 Tweaks to remove old files
2021-06-08 Tweak... Everything, oh wow
2021-06-08 Add sponsorship button
2021-06-21 Add DRV vibration motor and adjust a few extra topics
2021-06-21 Bump XasCode
2021-06-21 Bump lzrtag-esp-components
2022-12-26 Oscilloscope test
